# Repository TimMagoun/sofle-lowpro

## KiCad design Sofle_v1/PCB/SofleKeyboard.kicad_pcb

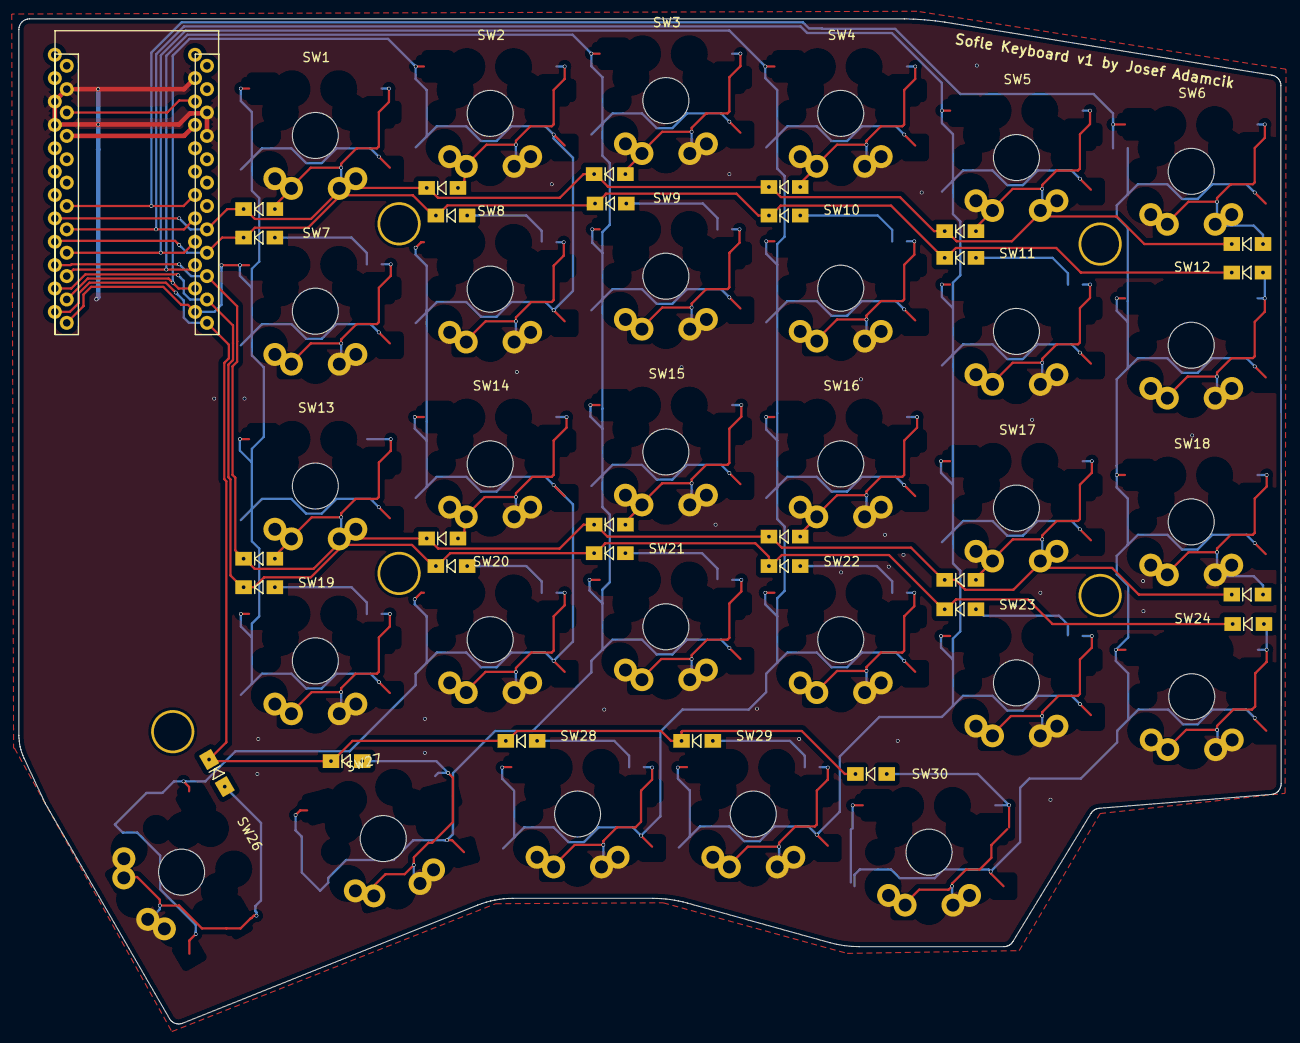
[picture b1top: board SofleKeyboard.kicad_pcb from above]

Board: 2 copper layers, 137.2 x 109.2 mm, 64 parts (0 on the bottom side), 41 nets.

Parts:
D1, D2, D3, D4, D5, D6, D7, D8, D9, D10, D11, D12, D13, D14, D15, D16, D17, D18, D19, D20, D21, D22, D23, D24, D26, D27, D28, D29, D30: D; Diode_SOD123
SW1, SW2, SW3, SW4, SW5, SW6, SW7, SW8, SW9, SW10, SW11, SW12, SW13, SW14, SW15, SW16, SW17, SW18, SW19, SW20, SW21, SW22, SW23, SW24, SW26, SW27, SW28, SW29, SW30: SW_PUSH; gateron-ks27-reversible
TH3, TH4, TH5, TH6, TH7: HOLE; HOLE_M2_TH
U1: ProMicro

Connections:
GND: U1.3 (GND), U1.4 (GND), U1.23 (GND)
unnamed: D1.2 (A), SW1.2
unnamed: D2.2 (A), SW2.2
unnamed: D3.2 (A), SW3.2
unnamed: D4.2 (A), SW4.2
unnamed: D5.2 (A), SW5.2
unnamed: D6.2 (A), SW6.2
unnamed: D7.2 (A), SW7.2
unnamed: D8.2 (A), SW8.2
unnamed: D9.2 (A), SW9.2
unnamed: D10.2 (A), SW10.2
unnamed: D11.2 (A), SW11.2
unnamed: D12.2 (A), SW12.2
unnamed: D13.2 (A), SW13.2
unnamed: D14.2 (A), SW14.2
unnamed: D15.2 (A), SW15.2
unnamed: D16.2 (A), SW16.2
unnamed: D17.2 (A), SW17.2
unnamed: D18.2 (A), SW18.2
unnamed: D19.2 (A), SW19.2
unnamed: D20.2 (A), SW20.2
unnamed: D21.2 (A), SW21.2
unnamed: D22.2 (A), SW22.2
unnamed: D23.2 (A), SW23.2
unnamed: D24.2 (A), SW24.2
unnamed: D26.2 (A), SW26.2
unnamed: D27.2 (A), SW27.2
unnamed: D28.2 (A), SW28.2
unnamed: D29.2 (A), SW29.2
unnamed: D30.2 (A), SW30.2
col0: SW6.1, SW12.1, SW18.1, SW24.1, SW30.1, U1.18 (A1(PF6))
col1: SW5.1, SW11.1, SW17.1, SW23.1, SW29.1, U1.17 (A0(PF7))
col2: SW4.1, SW10.1, SW16.1, SW22.1, SW28.1, U1.16 (D15(PB1))
col3: SW3.1, SW9.1, SW15.1, SW21.1, SW27.1, U1.15 (D14(PB3))
col4: SW2.1, SW8.1, SW14.1, SW20.1, SW26.1, U1.14 (D16(PB2))
col5: SW1.1, SW7.1, SW13.1, SW19.1
row0: D1.1 (K), D2.1 (K), D3.1 (K), D4.1 (K), D5.1 (K), D6.1 (K), U1.8 (D5(PC6))
row1: D7.1 (K), D8.1 (K), D9.1 (K), D10.1 (K), D11.1 (K), D12.1 (K), U1.9 (D6(PD7))
row2: D13.1 (K), D14.1 (K), D15.1 (K), D16.1 (K), D17.1 (K), D18.1 (K), U1.10 (D7(PE6))
row3: D19.1 (K), D20.1 (K), D21.1 (K), D22.1 (K), D23.1 (K), D24.1 (K), U1.11 (D8(PB4))
row4: D26.1 (K), D27.1 (K), D28.1 (K), D29.1 (K), D30.1 (K), U1.12 (D9(PB5))

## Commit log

2022-07-30 changed footprint to ks 27 reversible
